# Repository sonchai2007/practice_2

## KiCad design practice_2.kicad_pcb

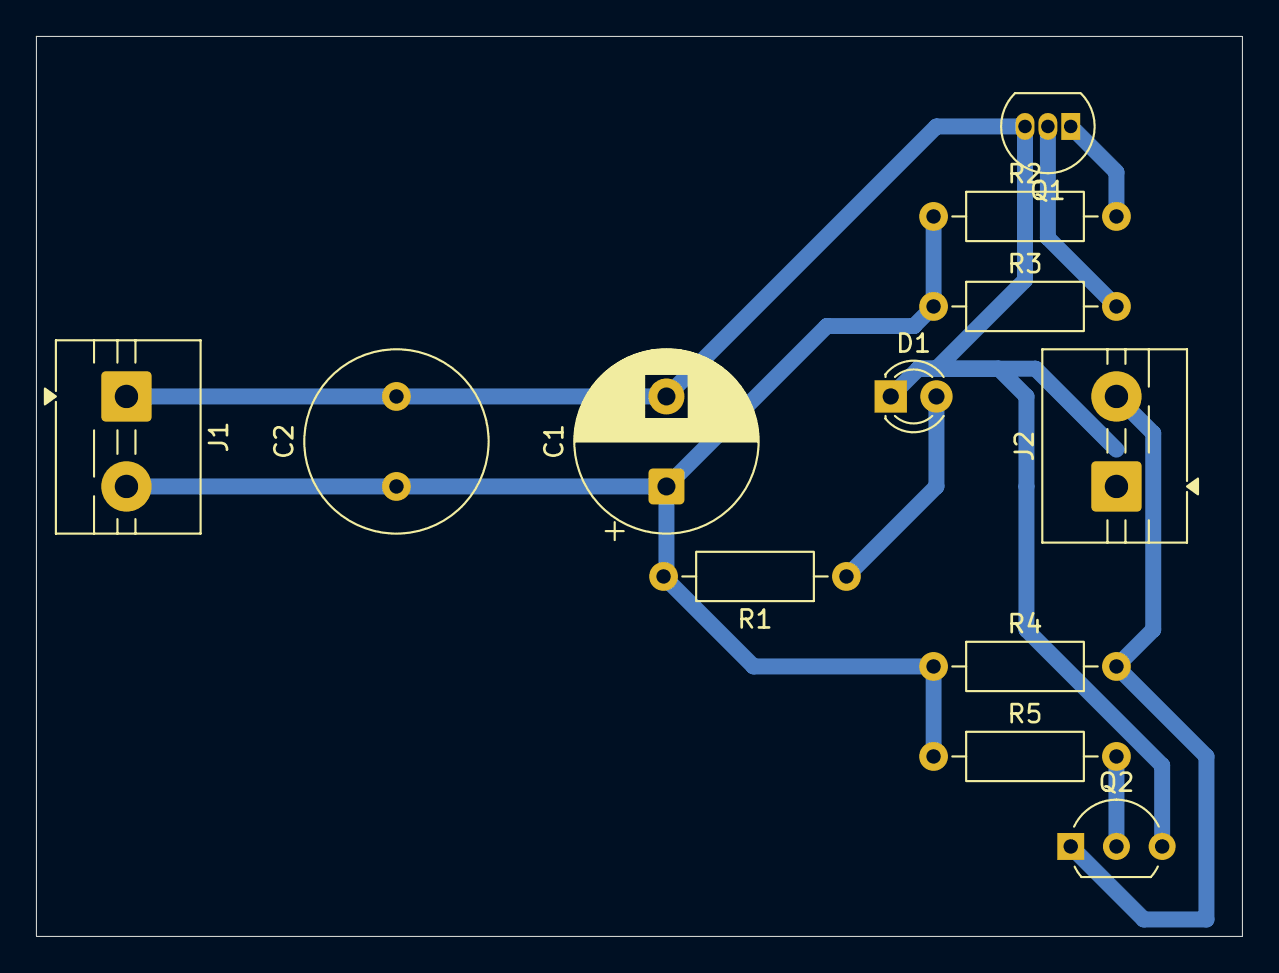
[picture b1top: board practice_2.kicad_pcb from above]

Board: 2 copper layers, 67.0 x 50.0 mm, 12 parts (0 on the bottom side), 7 nets.

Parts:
C1: C_Polarized; CP_Radial_D10.0mm_P5.00mm
C2: C; C_Radial_D10.0mm_H12.5mm_P5.00mm
D1: LED; LED_D3.0mm
J1, J2: Screw_Terminal_01x02; TerminalBlock_MaiXu_MX126-5.0-02P_1x02_P5.00mm
Q1: BC547; TO-92_Inline
Q2: Q_NPN_CBE; TO-92L_Inline_Wide
R1, R2, R3, R4, R5: R; R_Axial_DIN0207_L6.3mm_D2.5mm_P10.16mm_Horizontal

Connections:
/<NO NET>: J2.2 (Pin_2_2), Q2.1 (C), R4.2
GND: C1.2, C2.2, D1.1 (K), J1.1, Q1.3 (E), Q2.3 (E)
unnamed: D1.2 (A), R1.1
unnamed: Q1.2 (B), R3.2
unnamed: Q1.1 (C), R2.2
unnamed: Q2.2 (B), R5.2
VCC: C1.1, C2.1, J1.2, R1.2, R2.1, R3.1, R4.1, R5.1
